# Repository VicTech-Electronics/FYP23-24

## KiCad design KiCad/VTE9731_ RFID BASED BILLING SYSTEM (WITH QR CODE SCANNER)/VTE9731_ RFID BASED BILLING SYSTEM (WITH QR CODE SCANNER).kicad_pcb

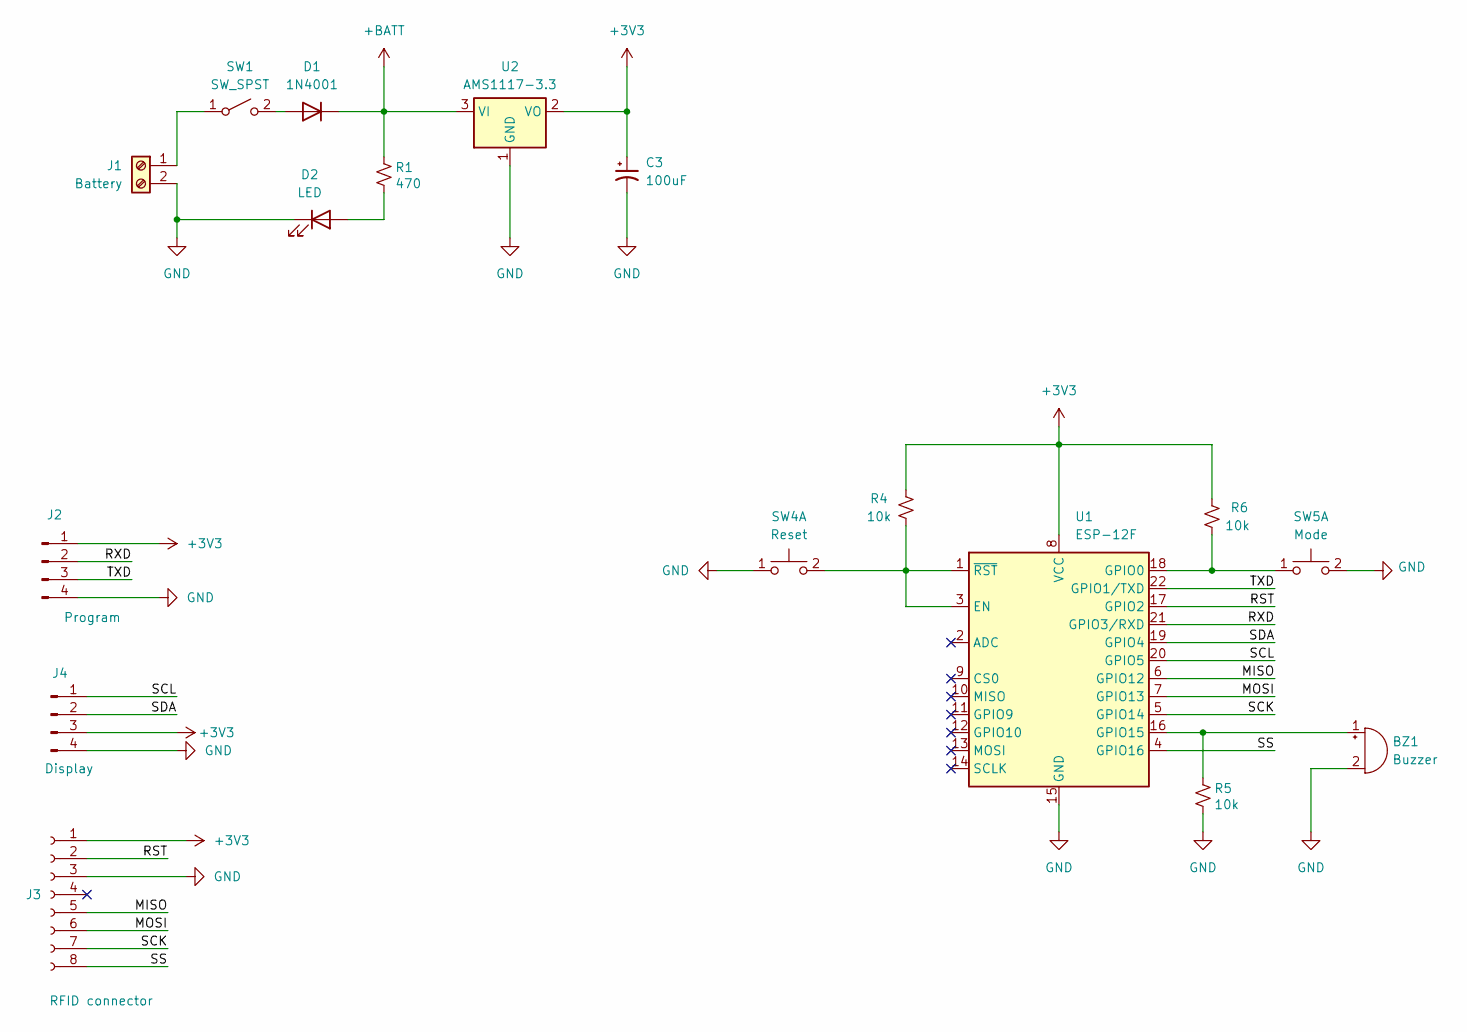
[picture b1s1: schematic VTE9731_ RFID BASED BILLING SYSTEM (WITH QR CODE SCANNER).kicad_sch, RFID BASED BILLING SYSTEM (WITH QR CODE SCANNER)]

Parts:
BZ1: Buzzer; Buzzer_15x7.5RM7.6
C3: 100uF; CP_Radial_D5.0mm_P2.50mm
D1: 1N4001; D_DO-41_SOD81_P10.16mm_Horizontal
D2: LED; LED_D5.0mm_Clear
J1: Battery; TerminalBlock_bornier-2_P5.08mm
J2: Program; PinHeader_1x04_P2.54mm_Vertical
J3: RFID connector; PinHeader_1x08_P2.54mm_Vertical
J4: Display; PinHeader_1x04_P2.54mm_Vertical
R1: 470; R_Axial_DIN0207_L6.3mm_D2.5mm_P10.16mm_Horizontal
R4, R5, R6: 10k; R_Axial_DIN0207_L6.3mm_D2.5mm_P10.16mm_Horizontal
SW1: SW_SPST; PinHeader_1x02_P2.54mm_Vertical
SW4: Reset; SW_PUSH_6mm
SW5: Mode; SW_PUSH_6mm
U1: ESP-12F; ESP-12E
U2: AMS1117-3.3; SOT-223-3_TabPin2

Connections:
+3V3: C3.1, J2.1, J3.1, J4.3, R4.2, R6.1, U1.8 (VCC), U2.2 (VO)
+BATT: D1.1 (K), R1.1, U2.3 (VI)
/MISO: J3.5, U1.6 (GPIO12)
/MOSI: J3.6, U1.7 (GPIO13)
/RST: J3.2, U1.17 (GPIO2)
/RXD: J2.2, U1.21 (GPIO3/RXD)
/SCK: J3.7, U1.5 (GPIO14)
/SCL: J4.1, U1.20 (GPIO5)
/SDA: J4.2, U1.19 (GPIO4)
/SS: J3.8, U1.4 (GPIO16)
/TXD: J2.3, U1.22 (GPIO1/TXD)
GND: BZ1.2 (-), C3.2, D2.1 (K), J1.2, J2.4, J3.3, J4.4, R5.2, SW4.1 (C), SW5.2 (D), U1.15 (GND), U2.1 (GND)
unnamed: BZ1.1 (+), R5.1, U1.16 (GPIO15)
unnamed: D1.2 (A), SW1.2 (B)
unnamed: D2.2 (A), R1.2
unnamed: J1.1, SW1.1 (A)
unnamed: R4.1, SW4.2 (D), U1.1 (~RST), U1.3 (EN)
unnamed: R6.2, SW5.1 (C), U1.18 (GPIO0)

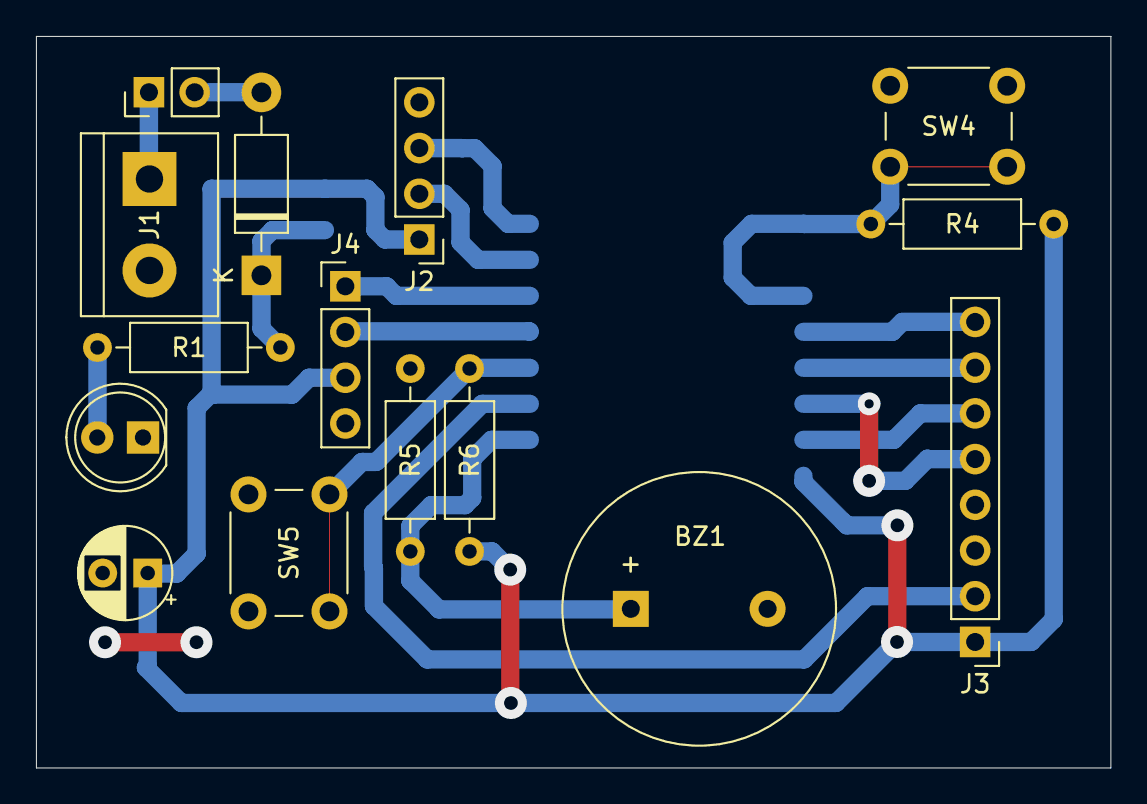
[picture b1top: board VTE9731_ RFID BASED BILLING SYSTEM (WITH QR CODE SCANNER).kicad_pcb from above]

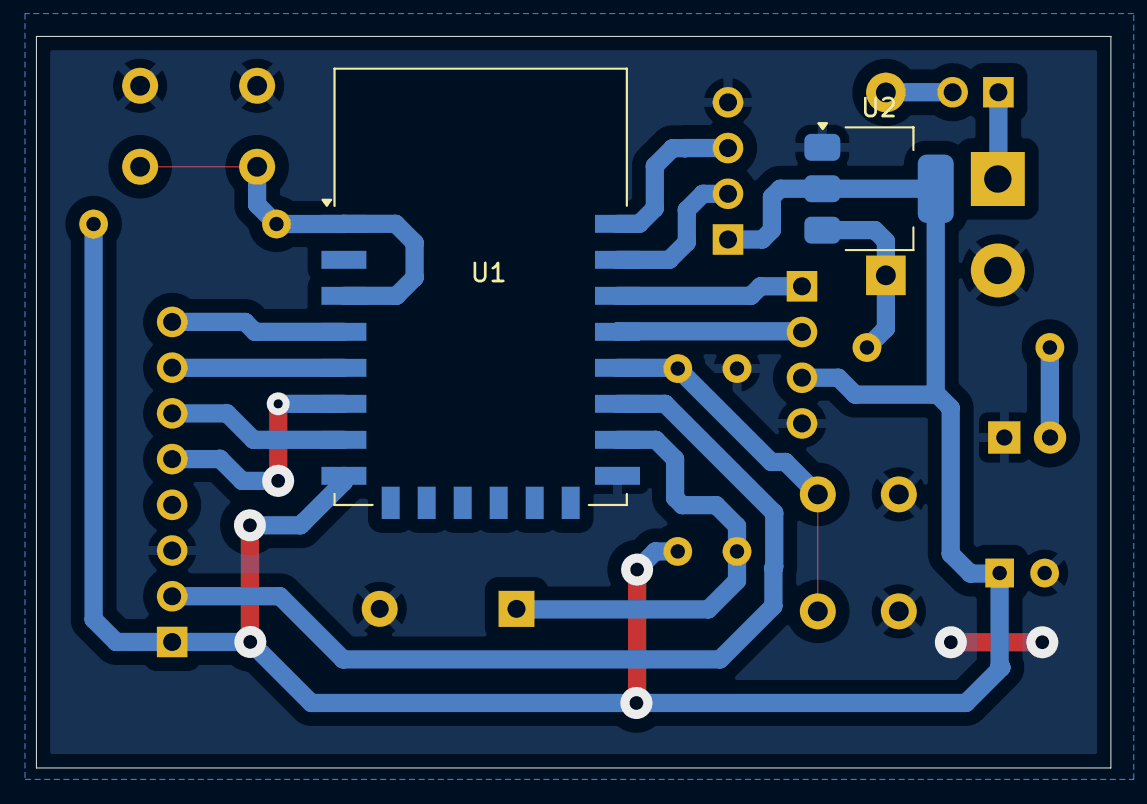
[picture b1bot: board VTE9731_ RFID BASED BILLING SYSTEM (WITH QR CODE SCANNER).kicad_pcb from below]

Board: 2 copper layers, 59.7 x 40.6 mm, 17 parts (2 on the bottom side), 18 nets.
